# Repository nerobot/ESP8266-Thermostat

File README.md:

# ESP8266-Thermostat

Thermostat temperature control system using ESP8266 serial wifi boards, Openhab, and DS1631 temperature sensing IC.

## Current Status

* Temperature Sensor Code and circuit
* Openhab setup for two temperature sensing boards and Raspberry Pi CPU temperature
* Thermostat control not setup

The project comes in 5 folders:

* The Openhab configuration files (a complete Openhab folder that can be copied and run)
* C code for the ESP thermometer devices
* C code for the ESP temperature control board (might not be up yet)
* Code for Node-Red
* Schematic and PCB designs

## Requirements

The ESP code was designed and compiled using the Windows SDK Toolkit available at http://www.esp8266.com/viewtopic.php?f=9&t=820 If installed correctly, you should have everything required to build and flash ESP8266 firmware.

## Installation

### Thermometer Sensor

* Load the projects into Eclipse
* Open file "/include/user_config.h" and change the #defines as necessary (I've left them to the default ones in the example)
* Open file "/user/user_main.c" and change the #define TOPIC to whatever is needed for that board
* Flash firmware

## Acknowledgements

* All the guys and galls over at esp8266.com for their hard on making these boards usable!
* Mikhail Grigorev for his work on the Windows Development Kit http://www.esp8266.com/viewtopic.php?f=9&t=820
* Tuan PM for his work on the native MQTT client for the esp8266 https://github.com/tuanpmt/esp_mqtt
* Anyone else I've missed out

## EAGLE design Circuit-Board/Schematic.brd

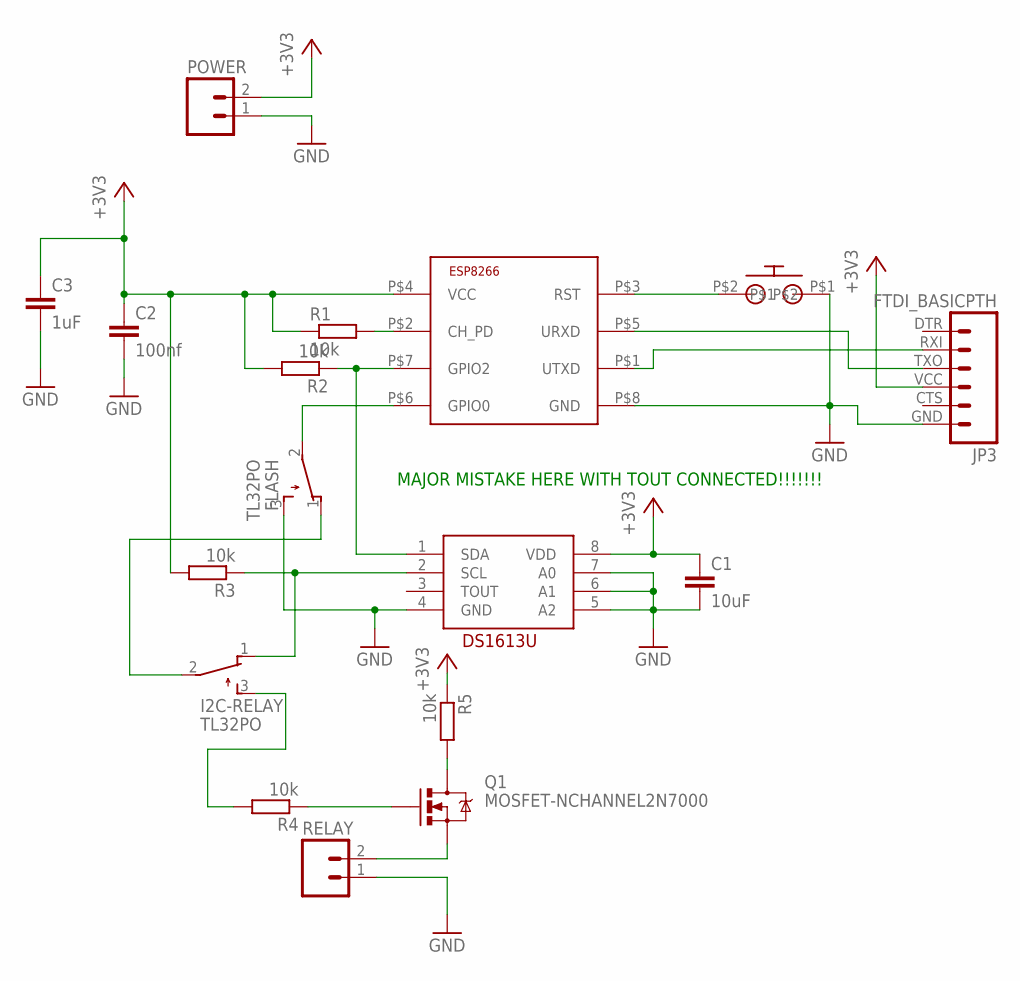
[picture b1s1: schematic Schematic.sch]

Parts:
C1: 10uF; C025-025X050
C2: 100nf; C025-025X050
C3: 1uF; C025-025X050
FLASH: TL32PO; TL3XPO
I2C-RELAY: TL32PO; TL3XPO
JP3: FTDI_BASICPTH; FTDI_BASIC
POWER: M02JST-PTH-VERT; JST-2-PTH-VERT
Q1: MOSFET-NCHANNEL2N7000; TO-92
R1, R2, R3, R4, R5: 10k; 0207/10
RELAY: M02JST-PTH-VERT; JST-2-PTH-VERT
RESET: TACT-SWITCH
U1: DS1631U+
U$1: ESP8266-01; ESP-01

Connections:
+3V3: C1.1, C2.1, C3.1, JP3.VCC (4), POWER.2, R1.1, R2.2, R3.2, R5.1, U1.8 (VDD), U$1.P$4 (VCC)
GND: C1.2, C2.2, C3.2, FLASH.3 (S), JP3.GND (6), POWER.1, RELAY.1, RESET.P$1, U1.4 (GND), U1.5 (A2), U1.6 (A1), U1.7 (A0), U$1.P$8 (GND)
unnamed: FLASH.2, U$1.P$6 (GPIO0)
unnamed: RESET.P$2, U$1.P$3 (RST)
unnamed: R2.1, U1.1 (SDA), U$1.P$7 (GPIO2)
unnamed: JP3.TXO (3), U$1.P$5 (URXD)
unnamed: JP3.RXI (2), U$1.P$1 (UTXD)
unnamed: FLASH.1 (O), I2C-RELAY.2
unnamed: R1.2, U$1.P$2 (CH_PD)
unnamed: I2C-RELAY.1 (O), R3.1, U1.2 (SCL)
unnamed: Q1.1 (S), RELAY.2
unnamed: Q1.2 (G), R4.1
unnamed: Q1.3 (D), R5.2
unnamed: I2C-RELAY.3 (S), R4.2

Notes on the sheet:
MAJOR MISTAKE HERE WITH TOUT CONNECTED!!!!!!!

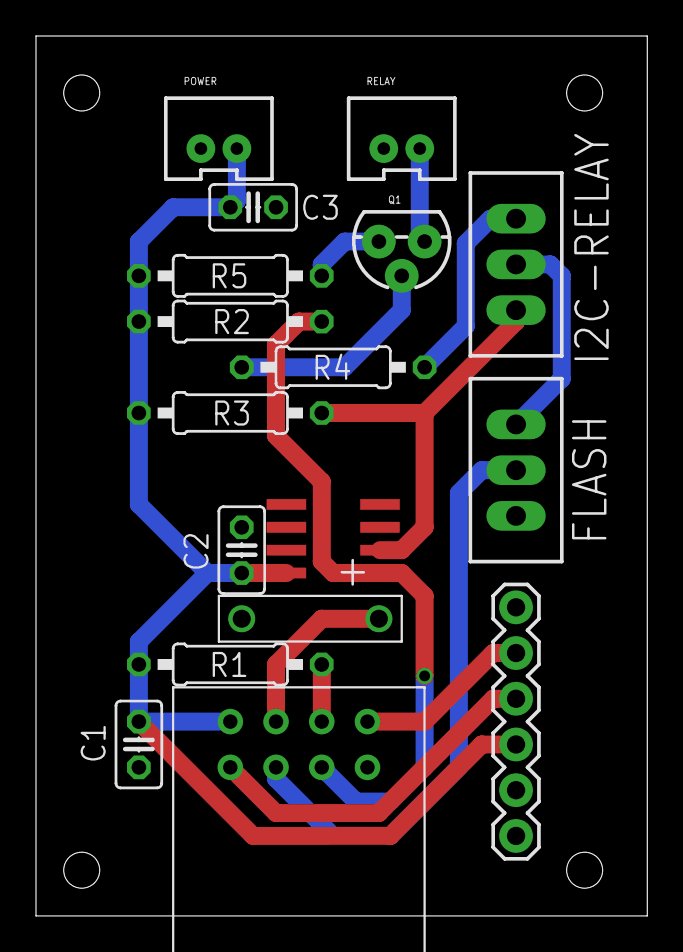
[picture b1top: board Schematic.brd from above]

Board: 2 copper layers, 34.0 x 48.9 mm, 17 parts (0 on the bottom side), 14 nets.

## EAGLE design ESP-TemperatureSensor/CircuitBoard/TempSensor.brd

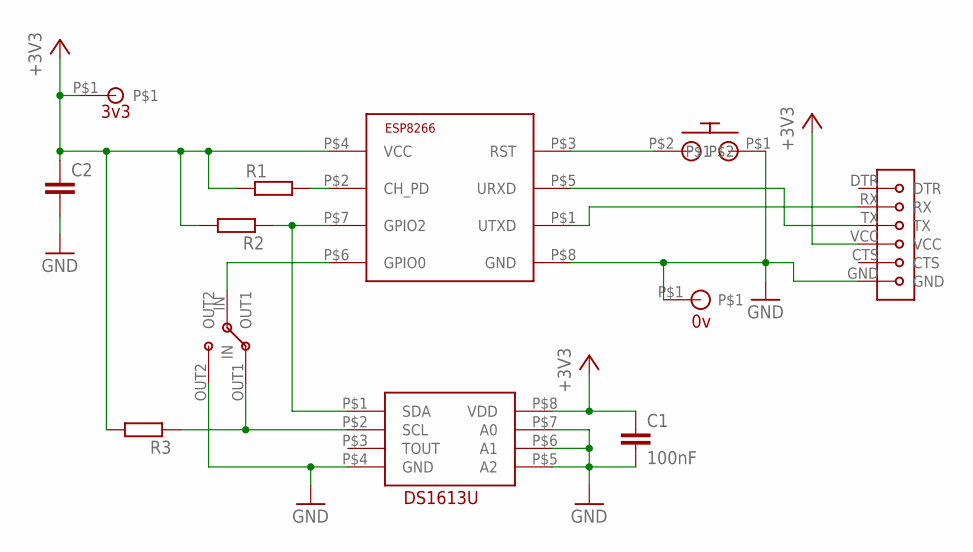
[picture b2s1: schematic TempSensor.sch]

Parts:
C1: 100nF; C025-025X050
C2: C-EU025-025X050; C025-025X050
R1, R2, R3: R-EU_0207/10; 0207/10
U$1: ESP8266-01; ESP-01
U$2: TACT-SWITCH
U$3: DS1631U-BREAKOUT
U$4: SPDT-SWITCH-1
U$5: FT232RL-ADAPTER
U$6: 3V3
U$7: 0V

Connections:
+3V3: C1.1, C2.1, R1.1, R2.2, R3.2, U$1.P$4 (VCC), U$3.P$8 (VDD), U$5.VCC, U$6.P$1
GND: C1.2, C2.2, U$1.P$8 (GND), U$2.P$1, U$3.P$4 (GND), U$3.P$5 (A2), U$3.P$6 (A1), U$3.P$7 (A0), U$4.OUT2, U$5.GND, U$7.P$1
unnamed: U$1.P$6 (GPIO0), U$4.IN
unnamed: U$1.P$3 (RST), U$2.P$2
unnamed: R3.1, U$3.P$2 (SCL), U$4.OUT1
unnamed: R2.1, U$1.P$7 (GPIO2), U$3.P$1 (SDA)
unnamed: U$1.P$5 (URXD), U$5.TX
unnamed: U$1.P$1 (UTXD), U$5.RX
unnamed: R1.2, U$1.P$2 (CH_PD)

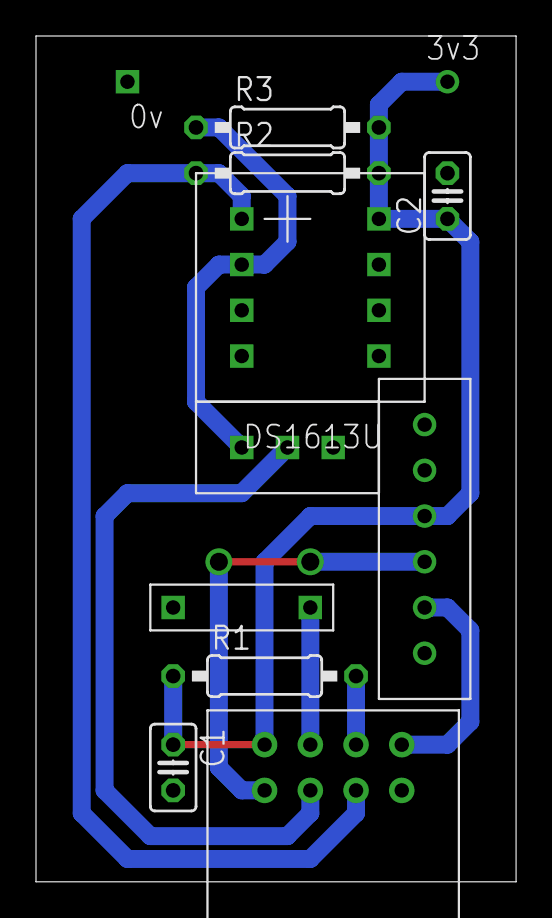
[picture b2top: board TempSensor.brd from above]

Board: 2 copper layers, 26.7 x 47.0 mm, 12 parts (0 on the bottom side), 9 nets.

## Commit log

2015-02-18 Added website of Windows Toolkit to README.md
2015-02-18 Uploaded barebones esp-mqtt example
    DO NOT USE!!!
2015-02-18 Updated to simple MQTT publishing example for testing
2015-02-24 Working Sensor Code
    ESP code for the temperature sensor now uploaded. Should be enough to
    compile and flash with small modifications.
2015-02-24 i2c library added
2015-02-24 Added further details to README
    Bit more details on installing the temperature sensing board code and
    the current status of the project.
2015-02-24 Created working Openhab config
2015-02-24 EagleCAD PCB Uploaded
2015-02-25 Uploaded circuit diagram and improved PCB design
    PCB design for simple prototyping fabing. Single sided with large
    tracks.
2015-02-25 Small change to PCB design
2015-02-25 Fixing issue with board upload
2015-03-03 Updated the circuit
    Updated the circuit diagram and created a better single sided PCB design
    for prototyping.
2015-03-03 Added #define for topic
2015-03-03 Small readme update
2015-03-17 New Circuit Board and Openhab Config
    A double sided circuit board has been designed and sent off for
    fabrication.
    Openhab has been reconfigured so that there are no rules and all
    calculations and rules are done in Node-Red
2015-03-17 Created Node-Red folder
    Node-Red is now used for the calculations and rules instead of Openhab.
2015-03-17 Image of PCB design uploaded
2015-03-17 Added screenshot of node-red schematic
2015-04-08 Updated circuit board
    Major error in circuit board design with second switch going to Tout
    instead of SCK on the DS1361.

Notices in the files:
parts and their libraries:
SparkFun-DiscreteSemi: Licensing: Creative Commons ShareAlike 4.0 International - https://creativecommons.org/licenses/by-sa/4.0
